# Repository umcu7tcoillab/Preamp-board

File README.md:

# Preamp board

## About us
This design has been made by the coil-lab of the High Field MRI Group of the UMC Utrecht in the Netherlands, where we make hardware to support our researchers. We are part of a research group which means we feel the need to open up some of our designs to whomever can make use of it, to further the research of MRI applications.

## The design
This project contains a preamp board made for our 7T Philips Achieva MRI system. It has been tested inside the magnetic field of the 7T MRI. 

The preamp board is used to connect the coil to the preamp. An optional T/Pi/matching network can be added as well for matching or preamp decoupling.

The design and subsequent drawing has been done in Kicad 5.1.5.

## Download
Gerber and BOM production files for the latest _field tested_ version of the PCB can be found in the 'Releases' page, or by following [this link](https://github.com/umcu7tcoillab/Preamp-board/releases/latest). 
You can also make your own production files by downloading the Kicad project and generating them, but these are not guaranteed to have been field tested.

## Images
**3D Image**

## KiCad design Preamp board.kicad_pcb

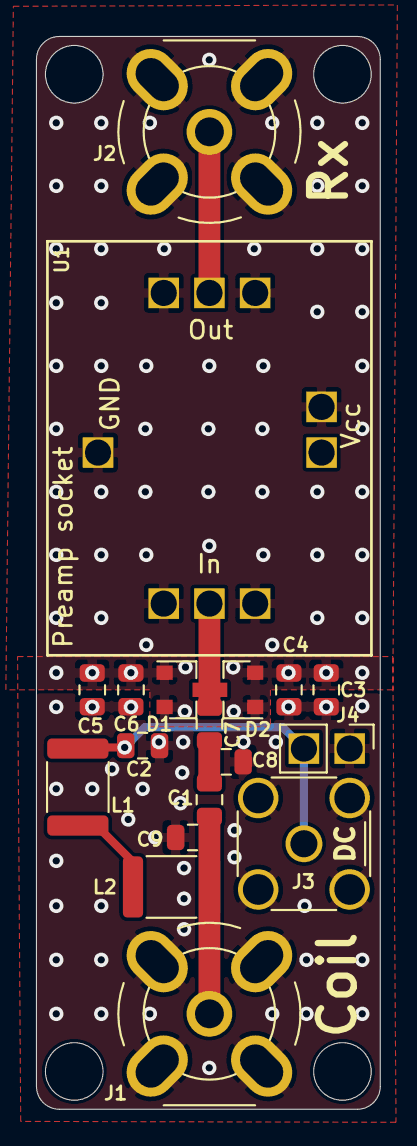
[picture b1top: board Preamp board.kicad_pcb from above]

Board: 2 copper layers, 19.1 x 59.6 mm, 23 parts (1 on the bottom side), 8 nets.

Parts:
C1, C8: T/pi; C_0805_2012Metric
C2, C3, C4, C5, C6: 10n; C_0805_2012Metric
C7: T/10n; C_0805_2012Metric
C9: pi; C_0805_2012Metric
D1, D2: BAV99; SOT-23
G1: LOGO; UMC_logo_small
H1, H2, H3, H4: M3; MountingHole_3.2mm_M3
J1: Coil; BNC_SMA_Vertical
J2: Rx; BNC_SMA_Vertical
J3: DC; SMA_Amphenol_132134-16_Vertical
J4: DC; Preci-dip_PinHeader_1x02_rect
L1, L2: 1u; L_1812_4532Metric
U1: Preamp; Preamp_socket

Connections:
GNDA: C3.2, C4.2, C5.2, C6.2, D1.1, D1.2, D2.1, D2.2, H3.1, H4.1, J2.2, U1.4
GNDS: C2.1, C3.1, C4.1, C5.1, C6.1, C8.1, C9.1, J1.2, J3.2, J4.1
unnamed: C1.1, C9.2, J1.1, L2.1
unnamed: C1.2, C7.1, C8.2
unnamed: C2.2, J3.1, J4.2, L1.2
unnamed: C7.2, D1.3, D2.3, U1.1
unnamed: J2.1, U1.3
unnamed: L1.1, L2.2

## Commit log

2020-02-26 Changed: Removed unnecessary references in file
2020-03-05 Changed: updated preamp footprint. Made 3D settings
2020-03-05 Updated LICENSE
2020-03-12 Changed: header hole size, header to preci-dip header
2020-03-19 Small changes
2021-11-24 Small changes. V0.2
2021-11-24 Updated to v1.0
2021-11-24 Updated version number on pcb to v1.0
2021-11-24 Updated version date
